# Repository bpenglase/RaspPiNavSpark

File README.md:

RaspPiNavSpark
==============

The NavSpark+RTC Adapter Board for the Raspberry Pi.

[Setup Instructions on my Wiki.](http://brandon.penglase.net/index.php?title=NavSpark_GPS%2BGLONASS_Stratum-1_NTP_Time_Source_with_a_Raspberry_Pi)

I do try to rebuild the instructions every one in a while, as I rebuild my unit from scratch. I may also do a new spin of the board for the 40pin headers at some point.

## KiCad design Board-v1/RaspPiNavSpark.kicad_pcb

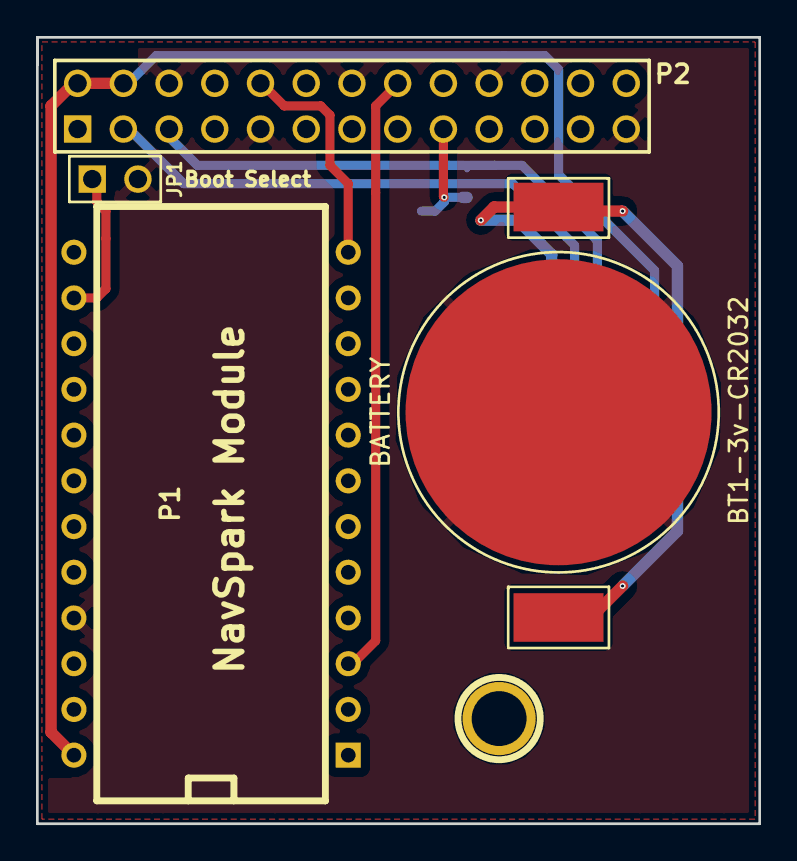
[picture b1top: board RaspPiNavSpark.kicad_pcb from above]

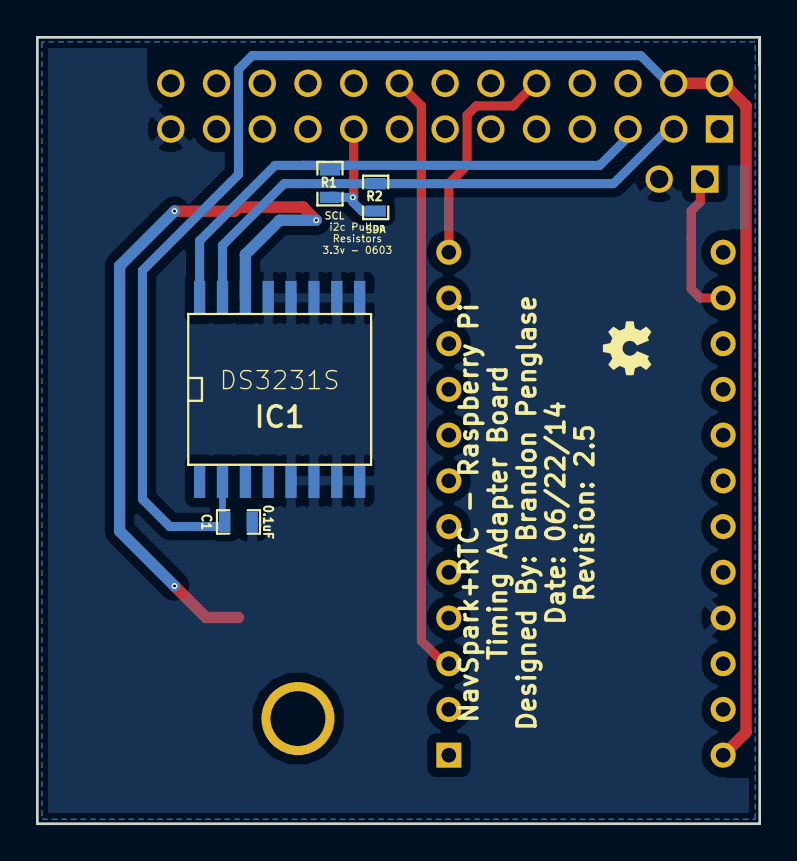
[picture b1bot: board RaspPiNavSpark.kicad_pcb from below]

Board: 2 copper layers, 40.1 x 43.7 mm, 8 parts (4 on the bottom side), 9 nets.

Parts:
BT1-3v-CR2032: BATTERY; BAT-HLD-001-2
C1: 0.1uF; SM0603_Capa
IC1: DS3231S; SO16L
JP1: JUMPER; PIN_ARRAY_2X1
P1: NavSpark Module; DIP-24__600
P2: CONN_13X2; pin_array_13x2
R1, R2: SM0603_Resistor

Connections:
+3.3V: P2.17, R1.1, R2.1
+5V: C1.2, IC1.2, P1.24, P2.2, P2.4
+BATT: BT1-3v-CR2032.1, IC1.14
/GPIO2-SDA: IC1.15, P2.3, R2.2
/GPIO3-SCL: IC1.16, P2.5, R1.2
/GPIO15-RXD: P1.12, P2.10
/GPIO23: P1.3, P2.16
GND: BT1-3v-CR2032.2, C1.1, IC1.5, IC1.6, IC1.7, IC1.8, IC1.9, IC1.10, IC1.11, IC1.12, IC1.13, JP1.2, P1.21, P2.6, P2.9, P2.14, P2.20, P2.25
unnamed: JP1.1, P1.14

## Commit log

2018-06-25 Board Schematics. Initial upload, sorry it's taken so long!
